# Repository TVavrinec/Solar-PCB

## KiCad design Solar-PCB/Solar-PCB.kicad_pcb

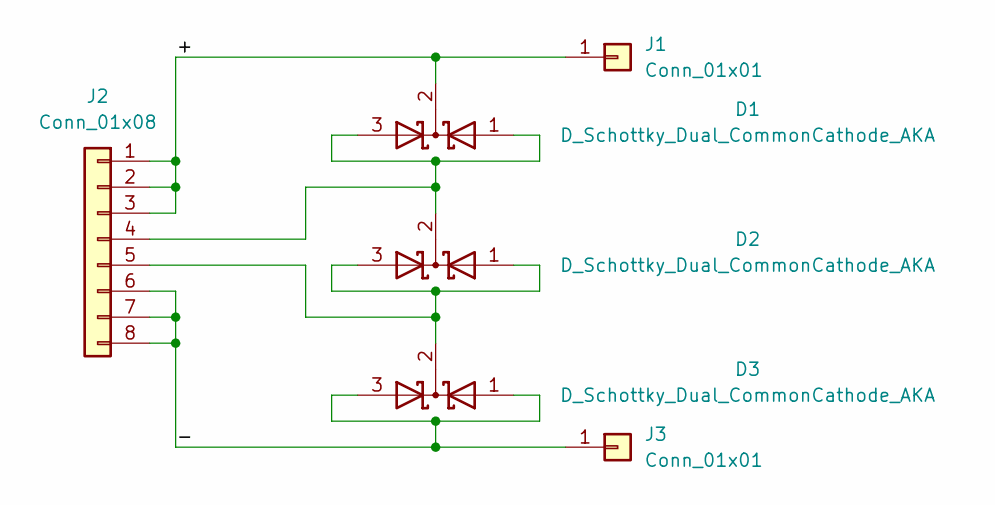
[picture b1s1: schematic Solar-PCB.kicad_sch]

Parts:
D1, D2, D3: D_Schottky_Dual_CommonCathode_AKA; TO-263-2; LCSC C181024
J1, J3: Conn_01x01; PinHeader_1x01_P2.54mm_Horizontal
J2: Conn_01x08; 8pin-revolver

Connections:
/+: D1.2 (K), J1.1, J2.1, J2.2, J2.3
/-: D3.1 (A), D3.3 (A), J2.6, J2.7, J2.8, J3.1
unnamed: D1.1 (A), D1.3 (A), D2.2 (K), J2.4
unnamed: D2.1 (A), D2.3 (A), D3.2 (K), J2.5

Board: 2 copper layers, 6 parts (0 on the bottom side), 4 nets, no tracks yet.

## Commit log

2025-04-04 Init
